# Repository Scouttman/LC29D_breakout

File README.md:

# LC29D_breakout
LC29D RTK gps breakout

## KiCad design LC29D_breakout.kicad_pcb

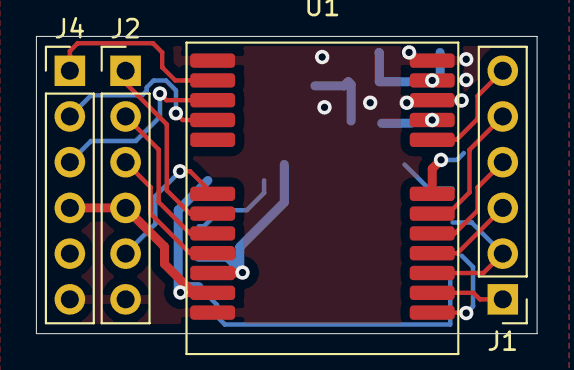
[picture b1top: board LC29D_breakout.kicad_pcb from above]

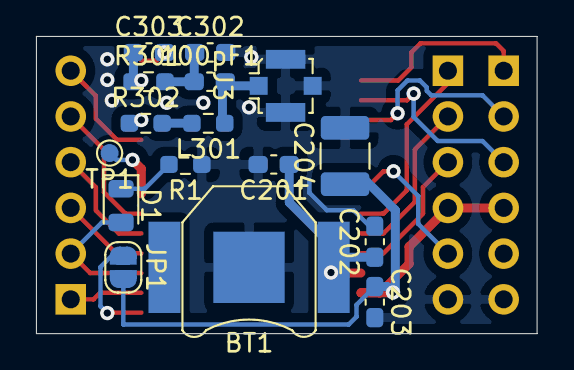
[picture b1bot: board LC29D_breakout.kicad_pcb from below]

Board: 2 copper layers, 27.8 x 16.5 mm, 20 parts (16 on the bottom side), 24 nets.

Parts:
100pF1: C301; C_0603_1608Metric_Pad1.08x0.95mm_HandSolder
BT1: Battery_Cell; BatteryHolder_Keystone_2998_1x6.8mm
C201: 4.7uF; C_0603_1608Metric_Pad1.08x0.95mm_HandSolder
C202, C203: 100nF; C_0603_1608Metric_Pad1.08x0.95mm_HandSolder
C204: 10uF; C_1210_3225Metric_Pad1.33x2.70mm_HandSolder
C302, C303: DNP; C_0603_1608Metric_Pad1.08x0.95mm_HandSolder
D1: LED; LED_0805_2012Metric
J1, J2, J4: Conn_01x06_Male; PinHeader_1x06_P2.54mm_Vertical
J3: Conn_Coaxial; U.FL_Molex_MCRF_73412-0110_Vertical
JP1: Jumper; SolderJumper-2_P1.3mm_Open_RoundedPad1.0x1.5mm
L301: 68nH; R_0603_1608Metric_Pad0.98x0.95mm_HandSolder
R1: R; R_0603_1608Metric_Pad0.98x0.95mm_HandSolder
R301: 0R; R_0603_1608Metric_Pad0.98x0.95mm_HandSolder
R302: 10R; R_0603_1608Metric_Pad0.98x0.95mm_HandSolder
TP1: TestPoint; TestPoint_Pad_D1.0mm
U1: LC29D

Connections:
/FwD: J1.1, U1.2
/I2C_SCL: J1.4, U1.5
/I2C_SDA: J1.5, U1.6
/LDA_enable: J4.1, U1.14
/N_Standby: J1.6, U1.8
/PPS: D1.2, J1.2, U1.3
/RF_in: C303.1, R301.1, U1.11
/RX_2: J4.3, U1.15
/TX_2: J4.2, U1.16
/VCC_RF: R302.1, U1.9
/V_Backup: BT1.1, C201.1, C202.1, U1.22
/WheelTick: J1.3, U1.4
GND: BT1.2, C201.2, C202.2, C203.2, C204.2, C302.2, C303.2, J2.6, J3.2, J4.6, R1.1, U1.10, U1.12, U1.13, U1.24
unnamed: 100pF1.1, C302.1, R301.2
unnamed: 100pF1.2, J3.1, L301.1
unnamed: D1.1, R1.2
unnamed: J2.1, U1.19
unnamed: J2.2, U1.20
unnamed: J2.3, U1.21
unnamed: J2.5, U1.18
unnamed: JP1.1, U1.1
unnamed: L301.2, R302.2
unnamed: TP1.1, U1.7
VCC: C203.1, C204.1, J2.4, J4.4, JP1.2, U1.23

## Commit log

2022-07-16 files
